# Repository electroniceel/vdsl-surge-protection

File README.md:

VDSL Surge Protection Adapter
=============================

|  |  |

Overview
--------

* Protects VDSL modems and routers from surges, like the ones induced by lightning
* Negligible loss of VDSL signal quality
* Compatible with ADSL, VDSL, VDSL2, VDSL2-Vectoring, 17a, 35b, probably also G.fast
* Not compatible with phone lines that have more than 60 VDC of idle voltage
   * These are for example ISDN lines (they usually have around 90 VDC idle voltage)
   * Also affects some old analog POTS lines

How to use
----------

* Disconnect all devices from your phone line and measure idle voltage between the two wires with a multimeter
* The idle voltage must not exceed 60 VDC
* Most lines used with *DSL modems today won't have any measurable DC voltage on them

* Install before your modem or router, using a RJ45 patch cord
* Connect the PE / Ground terminal to the earth bond of your building
  * Use a thick green/yellow wire, minimum 1.5mm² or AWG 15
  * Connect it for example to the PE of a power outlet
* When the PE terminal is not properly connected
  * the surge protection adapter will only protect from a very limited set of surge scenarios
  * it is much more prone to being damaged by a surge
  * so make sure PE is properly connected with a low impedance path to the same ground bond as the power supply of the modem
* Keep the line between the protection adapter and the modem/router short
  * a few meters is ok, but the longer this line, the more the signal is degraded
  * the length of wire between modem and protection adapter matters much more than the length between protection adapter and
    the outdoor cabinet of the phone company.
   
Schematics
----------

[PDF version of the schematics](https://github.com/electroniceel/vdsl-surge-protection/raw/master/schematics.pdf)

Theory of Operation
-------------------

#### Surges

* Surges can either be between the two phone line wires or between one or both lines against ground (PE)
* Surges can be either polarity. The protection adapter handles both.

#### What happens on a surge

* If any of these voltages exceeds about 80 V, the first thing to happen is that the respective set of TVS
  diodes (D1 to D6) begins to conduct. The current is about 1 mA at 80 V and will rise steeply with higher voltage.
* Due to the inductance of the phone wire, the maximum voltage of a surge is not reached immediately at the point
  of the protection adapter, but it rises more slowly, usually in the order of a few µs. 8 or 10 µs are the values
  used in common test pulse scenarios.
* When the voltage rises further, higher and higher current flows through the TVS diodes. At about 1 A flowing, the TBU devices begin
  to block. It takes them about 1 µs to completey block.
* The TBU devices can withstand up to 850 V
* When the voltage continues to rise and exceeds about 150 V, the Gas Discharge Tube will begin to conduct within nanoseconds
* The GDT will let the current flow into PE
* Once the GDT began to conduct (sparkover), the voltage across it will fall significantly; 10 V is mentioned in the datasheet for > 1 A
* The resistance of the phone line and the fuses, combined with the low arc voltage of the GDT, will even for very strong surges
  ensure that the voltage across the TBU does not exceed 850 V.
* This limits the voltage that reaches the modem / router on the protected port to about 90 to 100 V, which all modems must survive
  to be compliant with the respective telecom standards.

#### Fuses
  
* If the surge results in much higher current than 2 A for some time, one or both fuses will blow and break the current flow.
* This is mostly to protect the phone wire, as getting it replaced will probably be more expensive and time consuming than replacing
  a blown modem / router
* The GDT degrades physically while it conducts. The fuses also act as an indicator for overload conditions. If they should ever blow,
  it is best to replace all components of the surge protection adapter to ensure continued proper operation and low insertion loss

#### Surge strength
  
* This protection adapter is only intended to protect from surges induced into the phone lines by a lightning strike near the phone lines
* The fuses are rated for a maximum breaking capability of 60 A at 600 V. A direct lightning strike into the phone line will lead to several
  magnitudes more of current flowing and will not be stopped by the fuses or the rest of the protection adapter. Instead the phone lines will be vaporized, no matter if you have a protection adapter installed or not.

#### Effects on the signal
  
* During regular operation the TBU devices conduct, but introduce about 10 Ω resistance each
* Phone lines usually have resistances up into the Kiloohm range, so the DSL standards are designed to deal with it
* But capacitances, combined with the line resistance, act as low-pass filters and degrade the signal
* So any additional capacitance should be avoided. Special low capacitance diodes are used to employ this.
* The capacitance of a longer wire between protection adapter and modem would also create such a filter effect

#### TVS overload

* The TVS diodes can be damaged when they conduct for longer than a few µs and the TBU does not stop the current, 
  for example because less than 1 A is flowing or the adapter is installed backwards
* This can happen for voltages between about 80 V and 100 V
* This is the main reason this adapter should not be used on phone lines with higher idle voltage

Signal degradation
------------------

* I have measured the effects on the signal quality on several different phone lines with different modems / routers
* Maximum possible speed as shown by the modem was affected by about 2 % at most
* Publishing this data is still TODO

Procuring Parts and Building
----------------------------

#### BOM

* All Parts, except the Metz screw terminals, are available at Mouser
* The Metz screw terminals are available at Digikey and Reichelt
* The RJ45 from TE can be replaced by a cheaper pin compatible alternative available at LCSC
* Do not forget to order the case and the pluggable screw terminal (just the socket for it is on the PCB and on the BOM)

[See interactive BOM for details](https://htmlpreview.github.io/?https://github.com/electroniceel/vdsl-surge-protection/blob/master/bom/ibom.html)

#### PCBs

* The PCB is designed to fit into a Hammond 1593LBK case
* There are 3 PCBs: the main PCB and two small PCBs that are used as front panels for the Hammond case
* You can skip ordering the front panel PCBs if you want to mill out the space for the connectors yourself, Hammond ships the case with 
  blank front panels
* The gerber directory contains gerber zips ready to order
* The main PCB has not-plated-through holes (NPTH) for better mounting of the RJ45 connectors, they are in different .drl files. Better notify
  your board house about that
* There is the necessary position marker for JLCPCB to put their manufacturing number on the backside of the front panel PCBs. So check the
  respective option when ordering there.
* Mechanical design assumes all PCBs to be 1.6mm thickness

Testing 
-------

* This adapter was not tested in with actual lightning or simulated surge impulses
* Just the response until GDT sparkover was tested
* If you happen to have access to suitable surge testing equipment and want to help, please contact me. I can ship you samples for testing.

License
-------

This work is licensed under a [Creative Commons Attribution 4.0 International License](https://creativecommons.org/licenses/by/4.0/).

Please link to https://github.com/electroniceel/vdsl-surge-protection or https://git.io/JfI1V for attribution.

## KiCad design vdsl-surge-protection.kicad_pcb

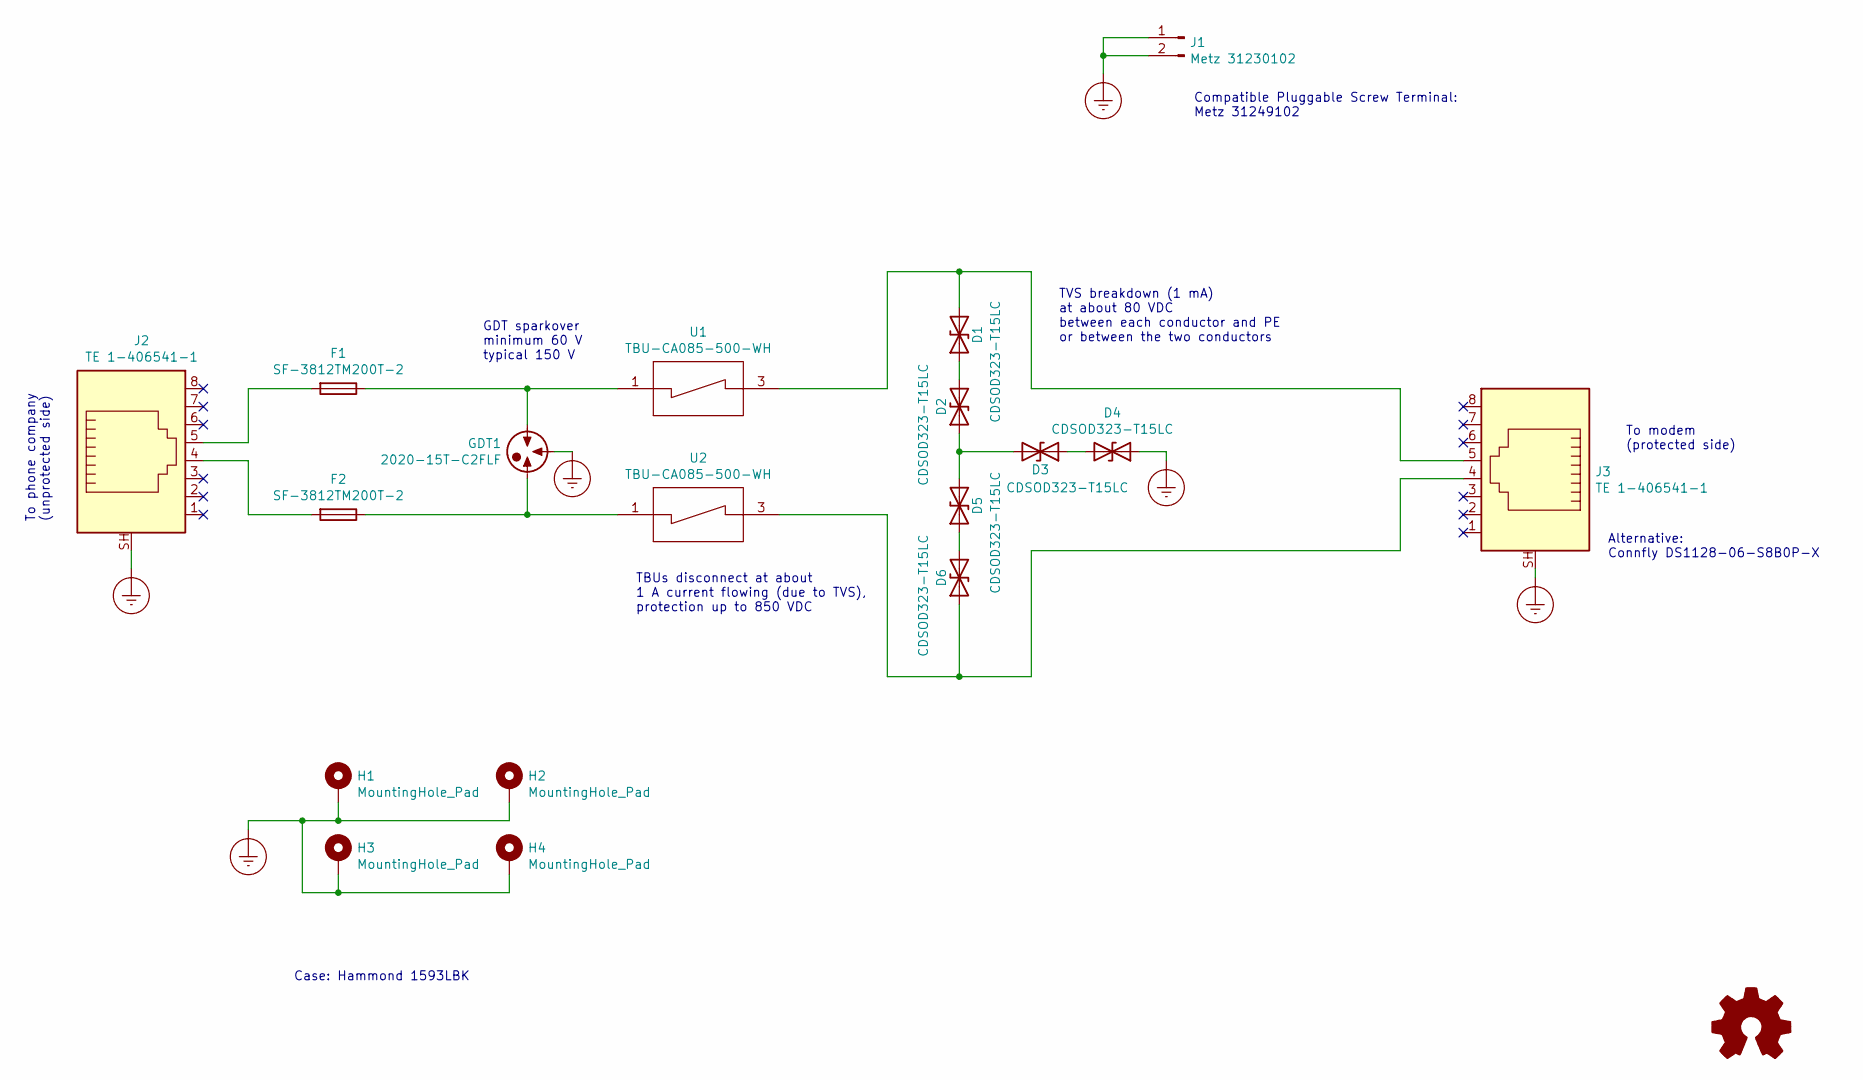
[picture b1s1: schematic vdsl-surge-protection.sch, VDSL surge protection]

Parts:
D1, D2, D3, D4, D5, D6: CDSOD323-T15LC; D_SOD-323_HandSoldering
F1, F2: SF-3812TM200T-2; Fuse_3812_HandSolder
GDT1: 2020-15T-C2FLF; 2020-xxT-C2x
H1, H2, H3, H4: MountingHole_Pad; MountingHole_3.7mm_Pad_Via
J1: Metz 31230102; mstba_2,5-2-g-5,08
J2, J3: TE 1-406541-1; CONN_1-406541-1
U1, U2: TBU-CA085-500-WH; TBU-CA

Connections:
Earth_Protective: D4.1 (A1), GDT1.2, H1.1, H2.1, H3.1, H4.1, J1.1, J1.2, J2.SH, J3.SH
unnamed: D1.1 (A1), D2.2 (A2)
unnamed: D1.2 (A2), J3.5, U1.3
unnamed: D2.1 (A1), D3.2 (A2), D5.2 (A2)
unnamed: D3.1 (A1), D4.2 (A2)
unnamed: D5.1 (A1), D6.2 (A2)
unnamed: D6.1 (A1), J3.4, U2.3
unnamed: F1.1, GDT1.1, U1.1
unnamed: F1.2, J2.5
unnamed: F2.1, GDT1.3, U2.1
unnamed: F2.2, J2.4

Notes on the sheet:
TVS breakdown (1 mA) at about 80 VDC between each conductor and PE or between the two conductors
TBUs disconnect at about 1 A current flowing (due to TVS), protection up to 850 VDC
GDT sparkover minimum 60 V typical 150 V
Alternative: Connfly DS1128-06-S8B0P-X
Case: Hammond 1593LBK
Compatible Pluggable Screw Terminal: Metz 31249102
To phone company (unprotected side)
To modem (protected side)

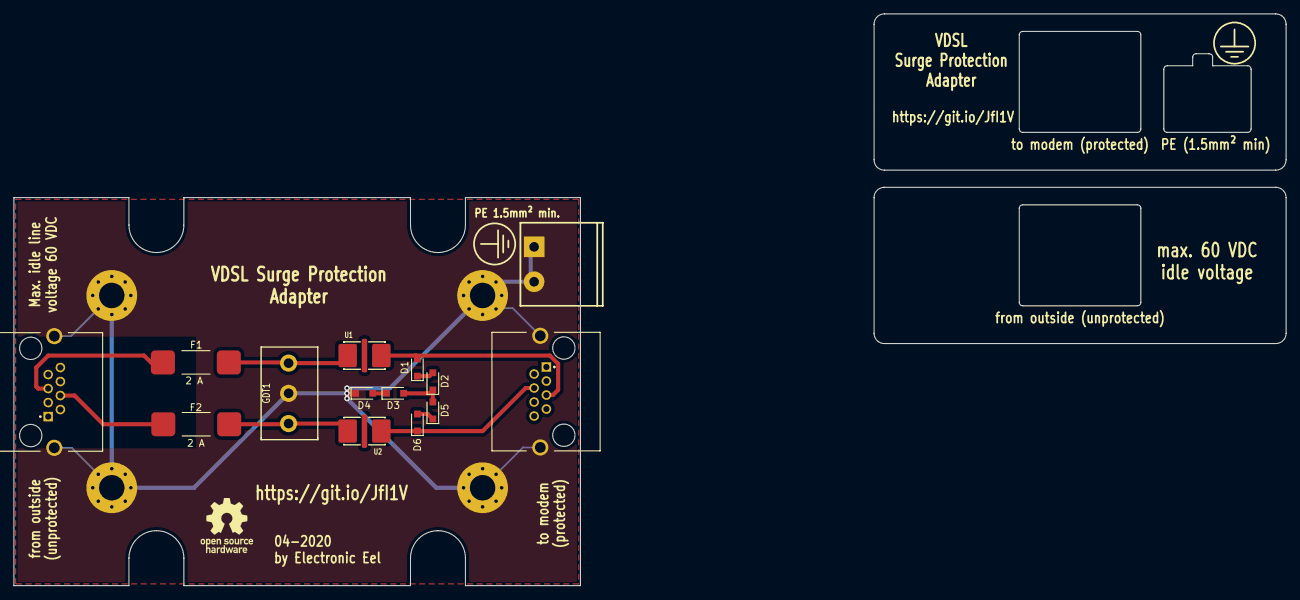
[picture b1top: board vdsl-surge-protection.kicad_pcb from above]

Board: 2 copper layers, 82.5 x 56.5 mm, 18 parts (0 on the bottom side), 11 nets.

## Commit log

2020-06-21 initial import
2020-06-21 fix iBOM URL
2020-06-21 add subsections to README.md
2020-06-21 better differentiate header styles in README.md
2020-06-21 add photos

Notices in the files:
vdsl-surge-protection.sch:
CC-BY-4.0
